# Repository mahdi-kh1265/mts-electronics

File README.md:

# mts-electronics

Analog RF, photodetector, and demodulation electronics for POSM's modulation-transfer spectroscopy (MTS) laser-locking system.

This repository contains two custom PCBs:

1. **`mts-clk`** — 10 MHz RF distribution and phase-control board for the EOM drive and MTS demodulation local oscillator.
2. **`mts-demod`** — photodiode front end, RF conditioning, analog mixer demodulation, and baseband error-signal generation.

The boards form the analog front end of POSM's rubidium MTS frequency lock.

---

## System Overview

# 1. `mts-clk` — 10 MHz Clock / Phase-Control Board

`mts-clk` takes a common 10 MHz RF source and generates the two coherent RF signals needed by the spectroscopy system:

* **EOM path** — drives the modulation chain associated with the electro-optic modulator.
* **DEMOD path** — provides the coherent local oscillator used by the analog MTS mixer.

Using a common source preserves coherence between modulation and demodulation.

# 2. `mts-demod` — Photodiode and Analog Demodulator

`mts-demod` converts the optical MTS signal into a low-frequency analog error signal suitable for digitization and feedback.

The board includes:

* FDS010 photodiode interface
* reverse-bias circuitry
* OPA858 transimpedance amplifier
* OPA695 second-stage RF amplifier
* 25 MHz RF cleanup filters
* RF splitting / diagnostic outputs
* conditioned 10 MHz LO path
* Mini-Circuits ADE-1+ mixer
* Mini-Circuits PLP-5+ post-mixer low-pass filter
* raw and demodulated monitor outputs

# 3. Repository Structure

```text
mts-electronics/
│
├── mts-clk/
│   ├── mts-clk.kicad_sch
│   ├── mts-clk.kicad_pcb
│   ├── mts-clk.kicad_pro
│   ├── libraries/
│   └── gerbers/
│
├── mts-demod/
│   ├── mts-demod.kicad_sch
│   ├── mts-demod.kicad_pcb
│   ├── mts-demod.kicad_pro
│   └── libraries/
│
├── LICENSE
└── README.md
```

The projects are currently stored in **KiCad 10** format.

---

# 4. Major Components

| Function                            | Part                      | Board       |
| ----------------------------------- | ------------------------- | ----------- |
| RF power splitter                   | Mini-Circuits TCP-2-10X   | `mts-clk`   |
| EOM-path RF amplifier               | ADI LTC6433-15            | `mts-clk`   |
| DEMOD-path RF amplifier             | ADI LTC6433-15            | `mts-clk`   |
| Voltage-controlled RF phase shifter | Mini-Circuits SCPHS-13.6+ | `mts-clk`   |
| Phase-control buffer                | TI OPA197                 | `mts-clk`   |
| Photodiode                          | Thorlabs FDS010           | `mts-demod` |
| First-stage TIA                     | TI OPA858                 | `mts-demod` |
| Second-stage amplifier              | TI OPA695                 | `mts-demod` |
| LO gain block                       | Mini-Circuits GVA-81      | `mts-demod` |
| Mixer                               | Mini-Circuits ADE-1+      | `mts-demod` |
| Post-mixer LPF                      | Mini-Circuits PLP-5+      | `mts-demod` |

Refer to the KiCad schematics for current component values and complete BOM information.

---

# 5. Bring-Up Sequence

These boards should be characterized independently before being connected to the complete laser lock.

## `mts-clk`

1. Verify resistance from each supply rail to ground before applying power.
2. Power the board with no external RF connections.
3. Verify all supply rails and amplifier bias conditions.
4. Apply a known 10 MHz RF input.
5. Measure the EOM output with an oscilloscope or spectrum analyzer.
6. Measure the DEMOD output.
7. Sweep the analog phase-control voltage.
8. Verify phase variation at 10 MHz relative to the EOM output.
9. Verify output amplitude remains within the intended range across the useful phase-control range.
10. Characterize phase versus control voltage and save the calibration curve.

## `mts-demod`

1. Verify all power rails before installing/connecting sensitive external hardware.
2. Verify photodiode reverse bias.
3. Illuminate the FDS010 with a controlled optical signal.
4. Measure the OPA858 TIA output.
5. Verify the OPA695 second-stage gain.
6. Verify the 25 MHz cleanup-filter response.
7. Apply a known 10 MHz DEMOD/LO signal.
8. Verify the GVA-81 LO chain.
9. Verify adequate LO drive at the ADE-1+.
10. Observe the raw mixer IF.
11. Verify the PLP-5+ output.
12. Sweep relative RF/LO phase and confirm the expected quadrature dependence.
13. Only after analog characterization, connect the ADC / FPGA system.

---

# 10. Characterization Data to Add

The schematic captures the intended design. Measured hardware performance should be added separately once boards are assembled.

Useful measurements include:

### CLK board

* EOM output power at 10 MHz
* DEMOD output power at 10 MHz
* EOM-to-DEMOD relative phase range
* phase versus control voltage
* amplitude versus phase-control voltage
* harmonic distortion
* broadband noise
* output return loss / matching

### DEMOD board

* TIA transimpedance
* TIA noise spectral density
* complete photodiode-path gain
* 25 MHz filter response
* mixer conversion gain/loss
* LO level at ADE-1+
* baseband transfer function
* analog error-signal noise
* output offset
* usable MTS discriminator slope
* channel saturation limits

Measured data should eventually be stored under a dedicated directory such as:

```text
measurements/
├── mts-clk/
│   ├── phase_vs_control_voltage.csv
│   ├── output_spectrum/
│   └── network_analyzer/
│
└── mts-demod/
    ├── tia_noise/
    ├── rf_transfer_function/
    ├── mixer_characterization/
    └── mts_error_signal/
```
# License

Released under the license included in [`LICENSE`](LICENSE).

---

## POSM

**Photonics and Optical Sciences Club at Minnesota**
University of Minnesota

[POSM website](https://posmphotonics.org/)

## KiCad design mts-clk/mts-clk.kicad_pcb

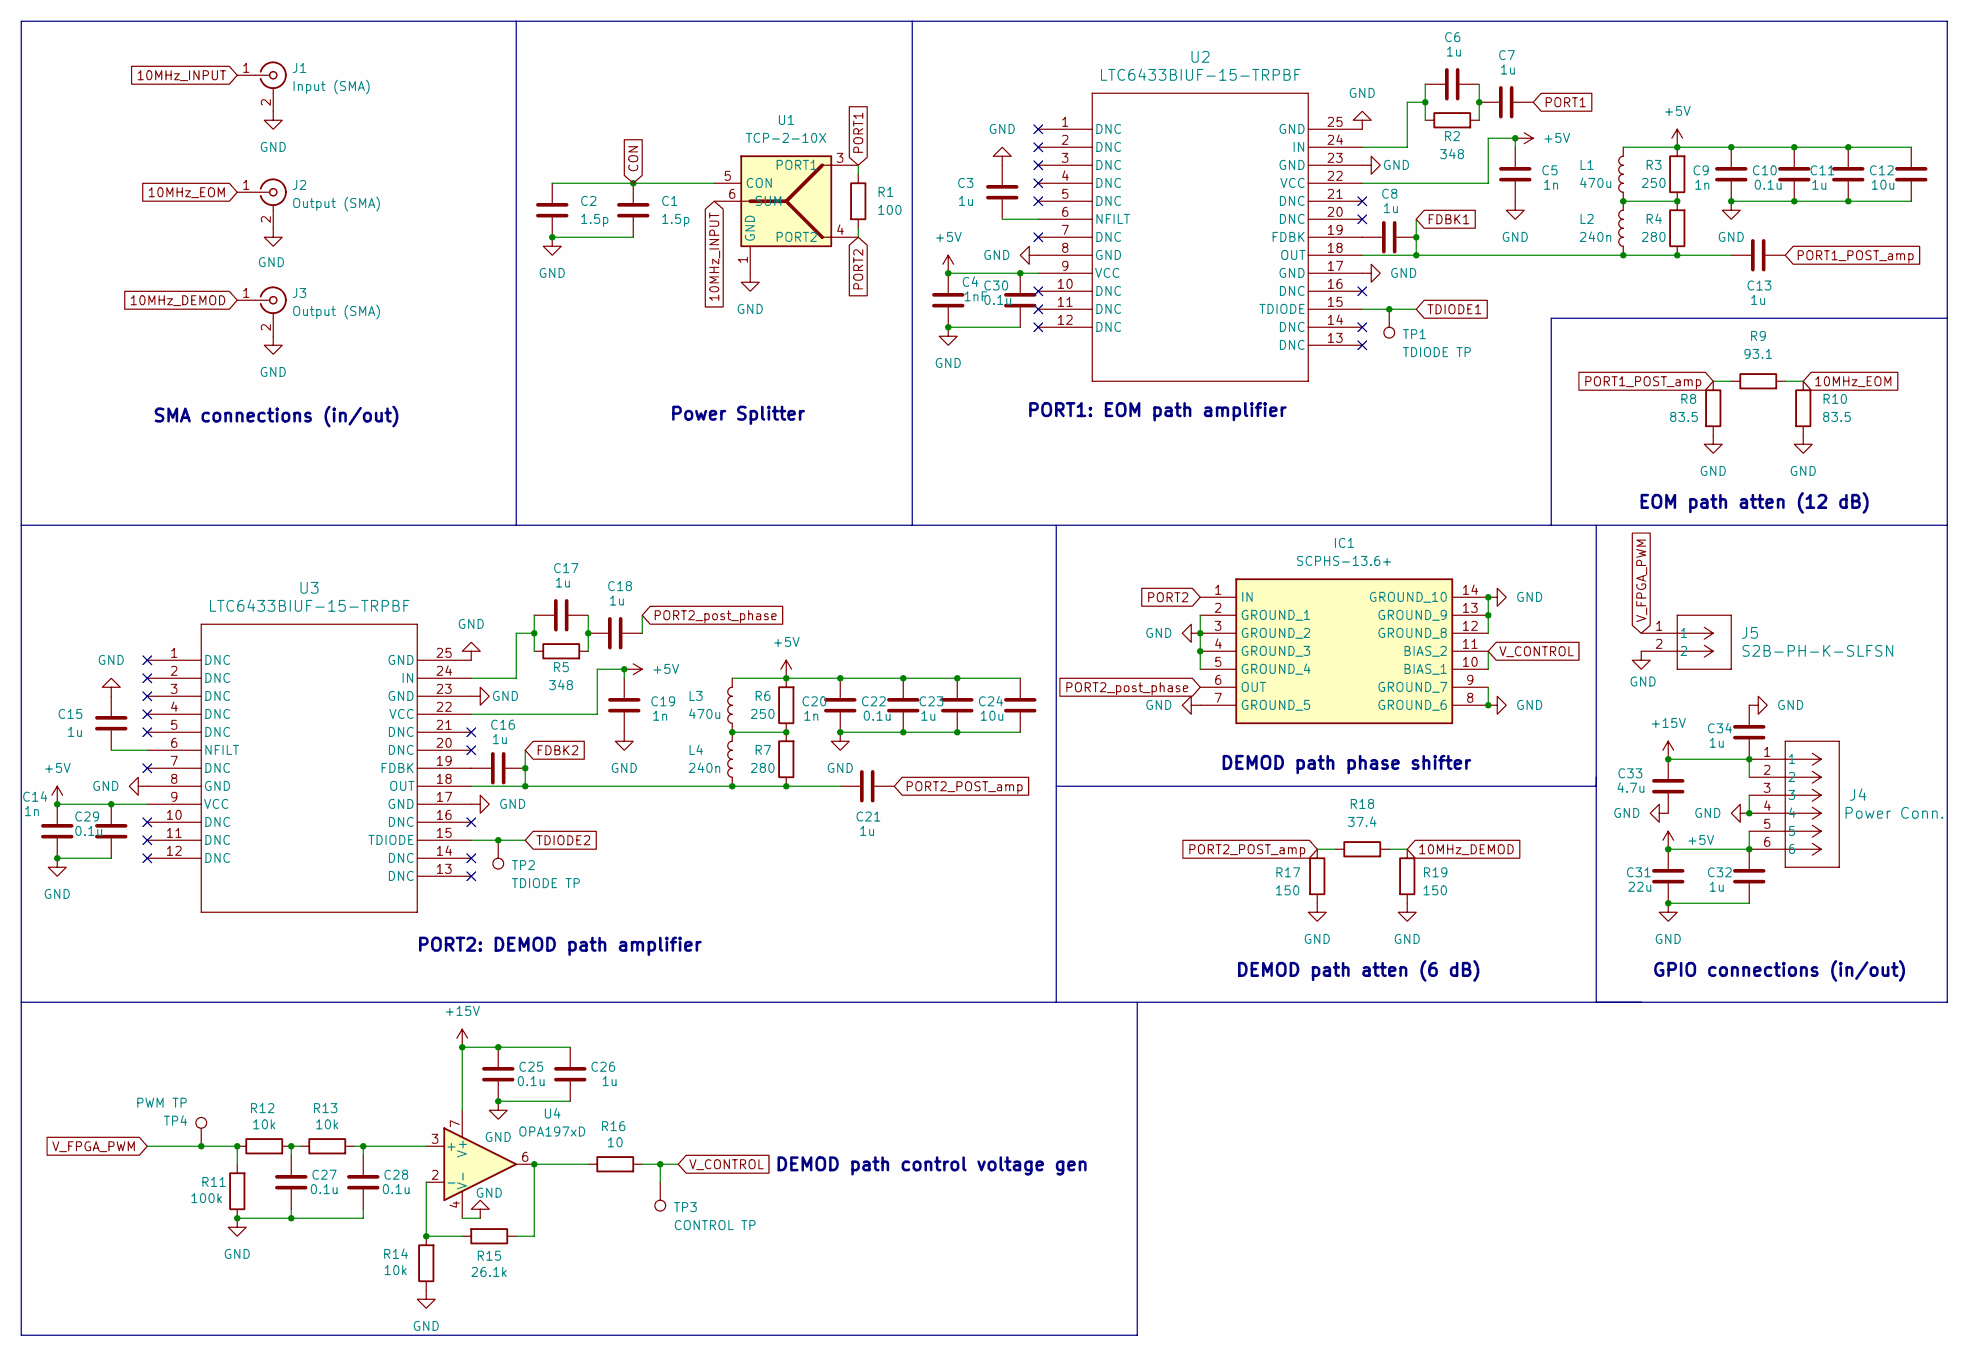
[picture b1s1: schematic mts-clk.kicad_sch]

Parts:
C1, C2: 1.5p; C_0402_1005Metric
C3, C6, C7, C8, C11, C13, C15, C16, C17, C18, C21, C23, C26: 1u; C_0805_2012Metric
C4: 1nF; C_0402_1005Metric
C5, C9, C14, C19, C20: 1n; C_0402_1005Metric
C10, C22, C29, C30: 0.1u; C_0603_1608Metric
C12, C24: 10u; C_0805_2012Metric
C25, C27, C28: 0.1u; C_0805_2012Metric
C31: 22u; C_1206_3216Metric
C32, C34: 1u; C_0603_1608Metric
C33: 4.7u; C_1206_3216Metric
IC1: SCPHS-13.6+; SCPHS136; Manufacturer_Part_Number SCPHS-13.6+
J1: Input (SMA); CONN_SMA-J-P-H-ST-TH1_SAI
J2, J3: Output (SMA); CONN_SMA-J-P-H-ST-TH1_SAI
J4: Power Conn.; CONN_SD-43045-005_06_MOL
J5: S2B-PH-K-SLFSN; CONN_S2B-PH-K-S_JST
L1, L3: 470u; L_Coilcraft_LPS5030
L2, L4: 240n; L_0603_1608Metric
R1: 100; R_0603_1608Metric
R2, R5: 348; R_0805_2012Metric
R3, R6: 250; R_0603_1608Metric
R4, R7: 280; R_0603_1608Metric
R8, R10: 83.5; R_0603_1608Metric
R9: 93.1; R_0603_1608Metric
R11: 100k; R_0603_1608Metric
R12, R13, R14: 10k; R_0603_1608Metric
R15: 26.1k; R_0603_1608Metric
R16: 10; R_0603_1608Metric
R17, R19: 150; R_0603_1608Metric
R18: 37.4; R_0603_1608Metric
TP1, TP2: TDIODE TP; TestPoint_Keystone_5015_Micro_Mini
TP3: CONTROL TP; TestPoint_Keystone_5015_Micro_Mini
TP4: PWM TP; TestPoint_Keystone_5015_Micro_Mini
U1: TCP-2-10X; Mini-Circuits_DB1627
U2, U3: LTC6433BIUF-15-TRPBF; UF_24_ADI
U4: OPA197xD; SOIC-8_3.9x4.9mm_P1.27mm

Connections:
10MHz_DEMOD: J3.1 (In), R18.2, R19.1
10MHz_EOM: J2.1 (In), R9.2, R10.1
10MHz_INPUT: J1.1 (In), U1.6 (SUM)
+5V: C4.2, C5.2, C9.2, C10.2, C11.2, C12.2, C14.2, C19.2, C20.2, C22.2, C23.2, C24.2, C29.2, C30.2, C31.2, C32.2, J4.5, J4.6, L1.2, L3.2, R3.2, R6.2, U2.9 (VCC), U2.22 (VCC), U3.9 (VCC), U3.22 (VCC)
+15V: C25.1, C26.1, C33.1, C34.1, J4.1, J4.2, U4.7 (V+)
FDBK1: C8.1, C13.2, L2.1, R4.1, U2.18 (OUT)
FDBK2: C16.1, C21.2, L4.1, R7.1, U3.18 (OUT)
GND: C1.2, C2.1, C3.1, C4.1, C5.1, C9.1, C10.1, C11.1, C12.1, C14.1, C15.1, C19.1, C20.1, C22.1, C23.1, C24.1, C25.2, C26.2, C27.2, C28.2, C29.1, C30.1, C31.1, C32.1, C33.2, C34.2, IC1.2 (GROUND_1), IC1.3 (GROUND_2), IC1.4 (GROUND_3), IC1.5 (GROUND_4), IC1.7 (GROUND_5), IC1.8 (GROUND_6), IC1.9 (GROUND_7), IC1.12 (GROUND_8), IC1.13 (GROUND_9), IC1.14 (GROUND_10), J1.2 (Ext), J1.3, J1.4, J1.5, J2.2 (Ext), J2.3, J2.4, J2.5, J3.2 (Ext), J3.3, J3.4, J3.5, J4.3, J4.4, J5.2, R8.2, R10.2, R11.1, R14.1, R17.2, R19.2, U1.1 (GND), U2.8 (GND), U2.17 (GND), U2.23 (GND), U2.25 (GND), U3.8 (GND), U3.17 (GND), U3.23 (GND), U3.25 (GND), U4.4 (V-)
unnamed: C6.1, C7.2, R2.2
unnamed: C17.1, C18.2, R5.2
unnamed: C27.1, R12.2, R13.1
unnamed: L1.1, L2.2, R3.1, R4.2
unnamed: L3.1, L4.2, R6.1, R7.2
unnamed: R15.1, R16.1, U4.6
unnamed: C8.2, U2.19 (FDBK)
unnamed: C6.2, R2.1, U2.24 (IN)
unnamed: C3.2, U2.6 (NFILT)
unnamed: C16.2, U3.19 (FDBK)
unnamed: C17.2, R5.1, U3.24 (IN)
unnamed: C15.2, U3.6 (NFILT)
unnamed: C28.1, R13.2, U4.3 (+)
unnamed: R14.2, R15.2, U4.2 (-)
PORT1: C7.1, R1.1, U1.3 (PORT1)
PORT1_POST_amp: C13.1, R8.1, R9.1
PORT2: IC1.1 (IN), R1.2, U1.4 (PORT2)
PORT2_POST_amp: C21.1, R17.1, R18.1
PORT2_post_phase: C18.1, IC1.6 (OUT)
TDIODE1: TP1.1 (1_1), U2.15 (TDIODE)
TDIODE2: TP2.1 (1_1), U3.15 (TDIODE)
V_CONTROL: IC1.10 (BIAS_1), IC1.11 (BIAS_2), R16.2, TP3.1 (1_1)
V_FPGA_PWM: J5.1, R11.2, R12.1, TP4.1 (1_1)

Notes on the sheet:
PORT1: EOM path amplifier
SMA connections (in/out)
DEMOD path phase shifter
DEMOD path control voltage gen
DEMOD path atten (6 dB)
GPIO connections (in/out)
Power Splitter
EOM path atten (12 dB)
PORT2: DEMOD path amplifier

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
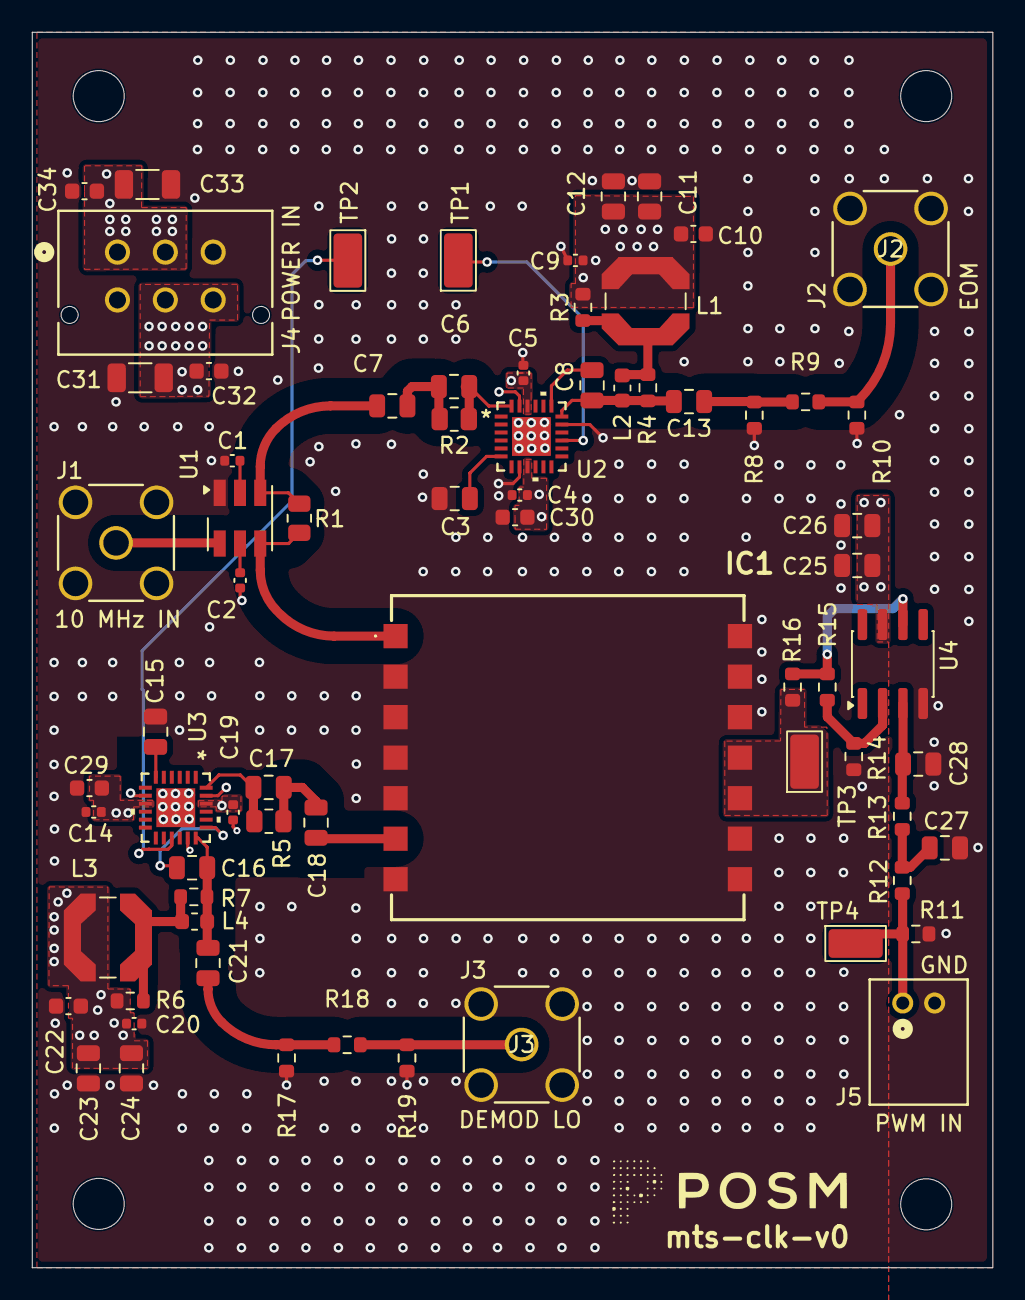
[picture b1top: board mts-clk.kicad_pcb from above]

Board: 4 copper layers, 60.2 x 77.5 mm, 71 parts (0 on the bottom side), 33 nets.

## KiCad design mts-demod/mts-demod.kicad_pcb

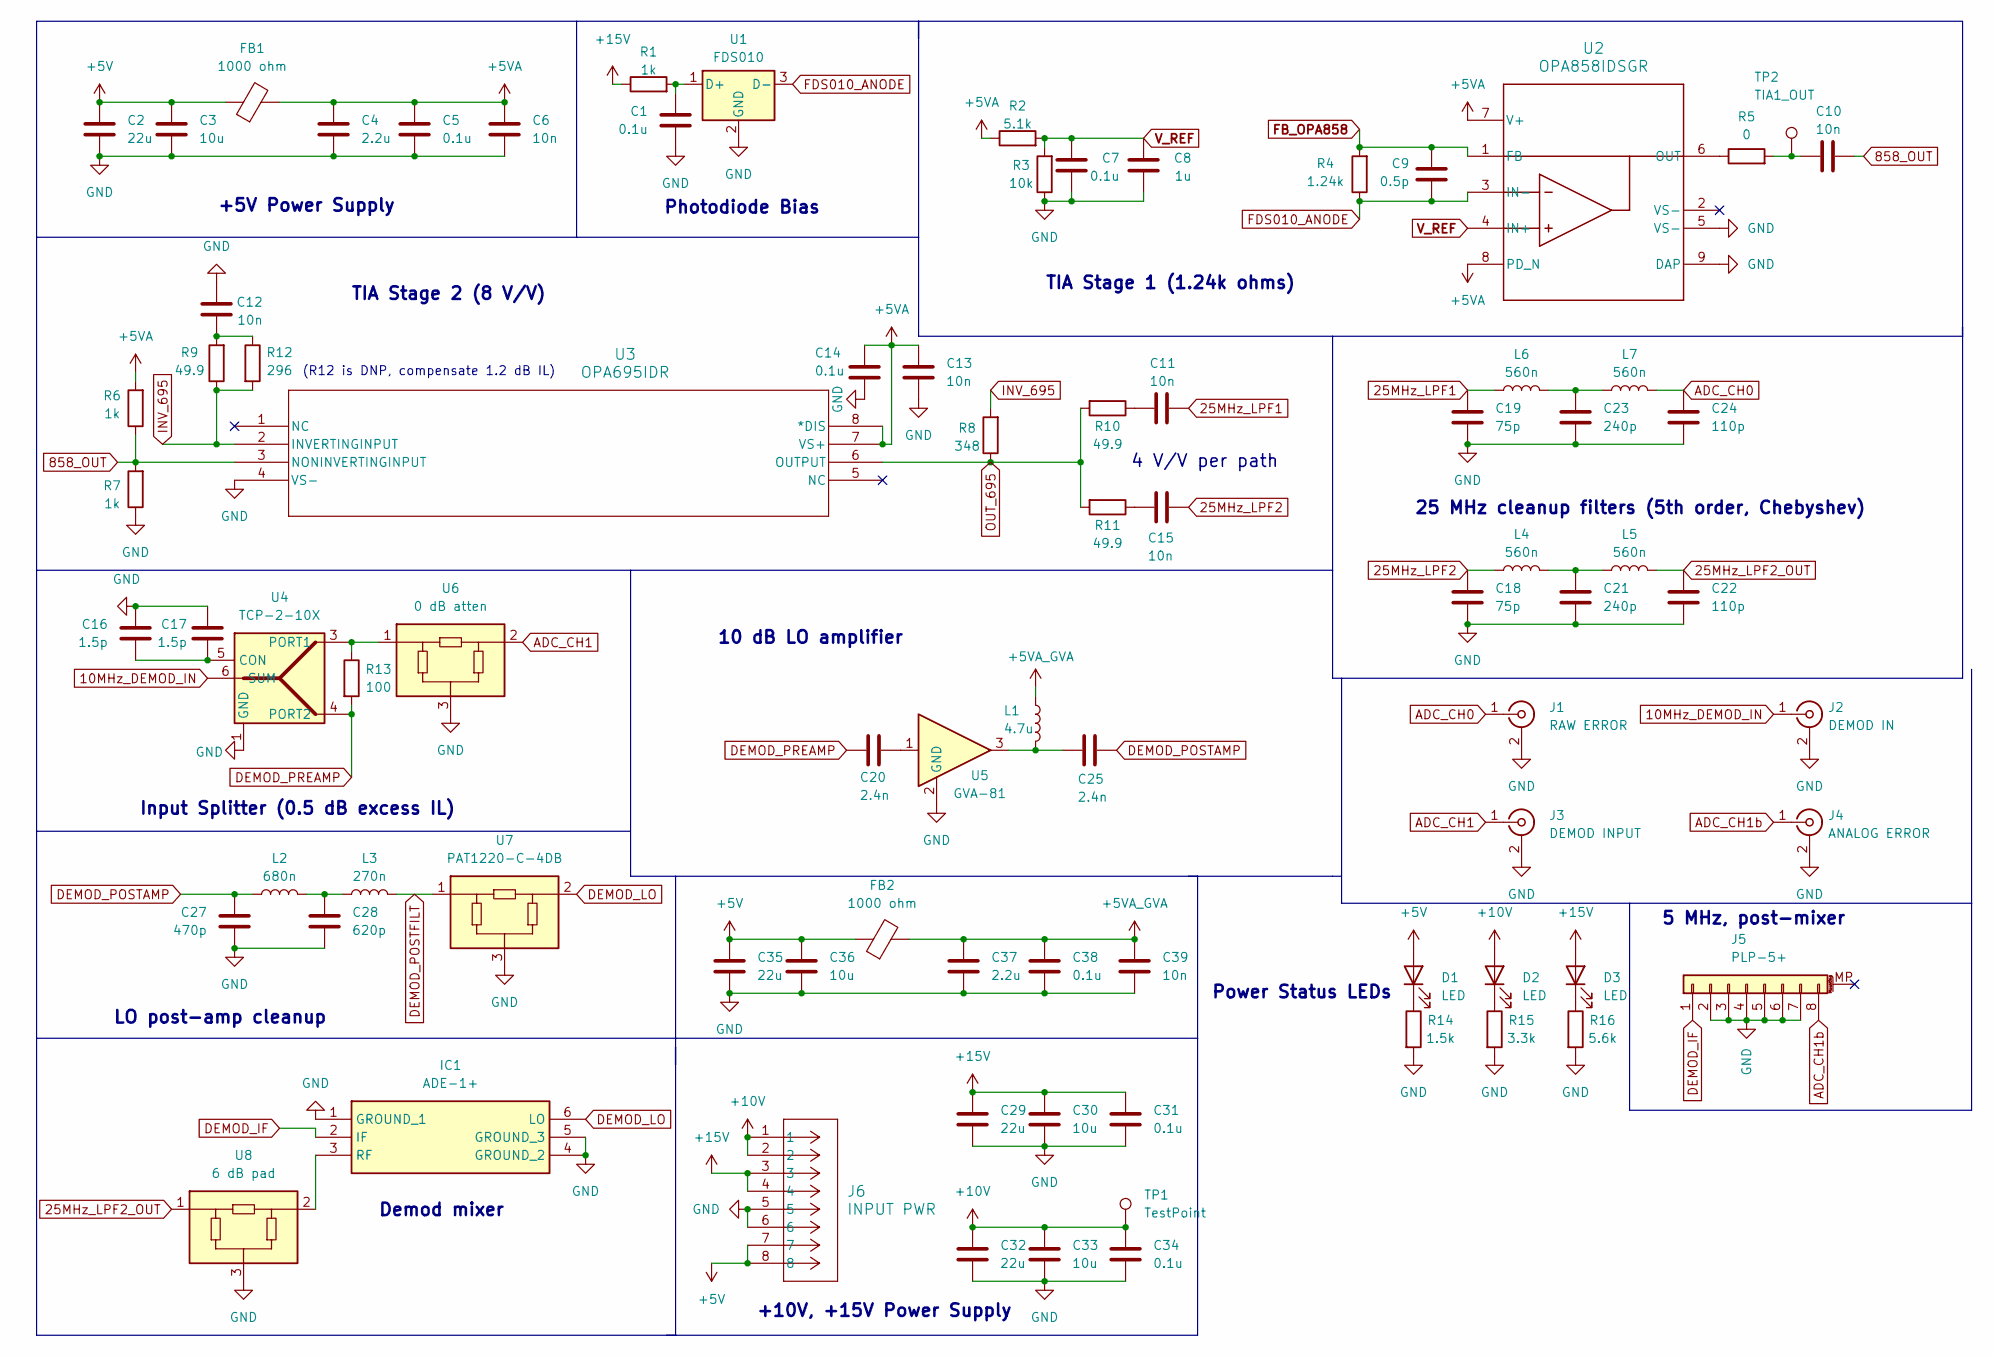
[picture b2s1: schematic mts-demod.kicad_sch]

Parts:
C1, C5, C7, C14, C31, C34, C38: 0.1u; C_0603_1608Metric
C2, C29, C32, C35: 22u; C_0805_2012Metric
C3, C30, C33, C36: 10u; C_0805_2012Metric
C4, C37: 2.2u; C_0603_1608Metric
C6, C10, C11, C12, C13, C15, C39: 10n; C_0402_1005Metric
C8: 1u; C_0603_1608Metric
C9: 0.5p; C_0402_1005Metric
C16, C17: 1.5p; C_0402_1005Metric
C18, C19: 75p; C_0805_2012Metric
C20, C25: 2.4n; C_0402_1005Metric
C21, C23: 240p; C_0805_2012Metric
C22, C24: 110p; C_0805_2012Metric
C27: 470p; C_0805_2012Metric
C28: 620p; C_0805_2012Metric
D1, D2, D3: LED; LED_0603_1608Metric
FB1, FB2: 1000 ohm; L_0805_2012Metric
IC1: ADE-1+; ADE1; Mouser Part Number 139-ADE-1
J1: RAW ERROR; CONN_SMA-J-P-H-ST-TH1_SAI
J2: DEMOD IN; CONN_SMA-J-P-H-ST-TH1_SAI
J3: DEMOD INPUT; CONN_SMA-J-P-H-ST-TH1_SAI
J4: ANALOG ERROR; CONN_SMA-J-P-H-ST-TH1_SAI
J5: PLP-5+; MINI-CIRCUITS_A01_CERN
J6: INPUT PWR; CONN_SD-43045-005_08_MOL
L1: 4.7u; L_0603_1608Metric
L2: 680n; L_0805_2012Metric
L3: 270n; L_0805_2012Metric
L4, L5, L6, L7: 560n; L_0805_2012Metric
R1, R6, R7: 1k; C_0603_1608Metric
R2: 5.1k; R_0603_1608Metric
R3: 10k; R_0603_1608Metric
R4: 1.24k; R_0603_1608Metric
R5: 0; R_0402_1005Metric
R8: 348; R_0402_1005Metric
R9: 49.9; C_0603_1608Metric
R10, R11: 49.9; R_0402_1005Metric
R12: 296; C_0603_1608Metric
R13: 100; C_0603_1608Metric
R14: 1.5k; C_0603_1608Metric
R15: 3.3k; C_0603_1608Metric
R16: 5.6k; C_0603_1608Metric
TP1: TestPoint; TestPoint_Keystone_5015_Micro_Mini
TP2: TIA1_OUT; TestPoint_Keystone_5015_Micro_Mini
U1: FDS010; TO-39-3
U2: OPA858IDSGR; DSG0008A
U3: OPA695IDR; D8
U4: TCP-2-10X; Mini-Circuits_DB1627
U5: GVA-81; SOT-89-3
U6: 0 dB atten; RF_Attenuator_Susumu_PAT1220
U7: PAT1220-C-4DB; RF_Attenuator_Susumu_PAT1220
U8: 6 dB pad; RF_Attenuator_Susumu_PAT1220

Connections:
10MHz_DEMOD_IN: J2.1 (In), U4.6 (SUM)
25MHz_LPF1: C11.2, C19.1, L6.1
25MHz_LPF2: C15.2, C18.1, L4.1
25MHz_LPF2_OUT: C22.1, L5.2, U8.1
858_OUT: C10.2, R6.1, R7.2, U3.3 (NONINVERTINGINPUT)
+5V: C2.1, C3.1, C35.1, C36.1, D1.2 (A), FB1.1, FB2.1, J6.7, J6.8; also elsewhere on the board
+5VA: C4.1, C5.1, C6.1, C13.1, C14.2, FB1.2, R2.1, R6.2, U2.7 (V+), U2.8 (PD_N), U3.7 (VS+), U3.8 (*DIS)
+5VA_GVA: C37.1, C38.1, C39.1, FB2.2, L1.1; also elsewhere on the board
+10V: C32.1, C33.1, C34.1, D2.2 (A), J6.1, J6.2, TP1.1; also elsewhere on the board
+15V: C29.1, C30.1, C31.1, D3.2 (A), J6.3, J6.4, R1.1; also elsewhere on the board
ADC_CH0: C24.1, J1.1 (In), L7.2
ADC_CH1: J3.1 (In), U6.2
ADC_CH1b: J4.1 (In), J5.8
DEMOD_IF: IC1.2 (IF), J5.1
DEMOD_LO: IC1.6 (LO), U7.2
DEMOD_POSTAMP: C25.1, C27.2, L2.1
DEMOD_POSTFILT: L3.2, U7.1
DEMOD_PREAMP: C20.2, R13.2, U4.4 (PORT2)
FB_OPA858: C9.2, R4.2, U2.1 (FB)
FDS010_ANODE: C9.1, R4.1, U1.3 (D-), U2.3 (IN-)
GND: C1.2, C2.2, C3.2, C4.2, C5.2, C6.2, C7.2, C8.2, C12.1, C13.2, C14.1, C16.2, C17.2, C18.2, C19.2, C21.2, C22.2, C23.2, C24.2, C27.1, C28.1, C29.2, C30.2, C31.2, C32.2, C33.2, C34.2, C35.2, C36.2, C37.2, C38.2, C39.2, IC1.1 (GROUND_1), IC1.4 (GROUND_2), IC1.5 (GROUND_3), J1.2 (Ext), J1.3, J1.4, J1.5, J2.2 (Ext), J2.3, J2.4, J2.5, J3.2 (Ext), J3.3, J3.4, J3.5, J4.2 (Ext), J4.3, J4.4, J4.5, J5.2, J5.3, J5.4, J5.5, J5.6, J5.7, J6.5, J6.6, R3.1, R7.1, R14.2, R15.2, R16.2, U1.2 (GND), U2.5 (VS-), U2.9 (DAP), U3.4 (VS-), U4.1 (GND), U5.2 (GND_2), U6.3, U7.3, U8.3; also elsewhere on the board
INV_695: R8.2, R9.1, R12.2, U3.2 (INVERTINGINPUT)
unnamed 22: C10.1, R5.2, TP2.1; also elsewhere on the board
unnamed: C11.1, R10.1
unnamed: C12.2, R9.2, R12.1
unnamed: C15.1, R11.1
unnamed: C20.1, U5.1
unnamed: C21.1, L4.2, L5.1
unnamed: C23.1, L6.2, L7.1
unnamed: C25.2, L1.2, U5.3
unnamed: C28.2, L2.2, L3.1
unnamed 31: D1.1 (K), R14.1; also elsewhere on the board
unnamed 32: D2.1 (K), R15.1; also elsewhere on the board
unnamed 33: D3.1 (K), R16.1; also elsewhere on the board
unnamed: IC1.3 (RF), U8.2
unnamed: C1.1, R1.2, U1.1 (D+)
unnamed: R5.1, U2.6 (OUT)
unnamed: R13.1, U4.3 (PORT1), U6.1
OUT_695: R8.1, R10.2, R11.2, U3.6 (OUTPUT)
V_REF: C7.1, C8.1, R2.2, R3.2, U2.4 (IN+)

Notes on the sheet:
(R12 is DNP, compensate 1.2 dB IL)
+10V, +15V Power Supply
+5V Power Supply
Photodiode Bias
Power Status LEDs
25 MHz cleanup filters (5th order, Chebyshev)
10 dB LO amplifier
4 V/V per path
LO post-amp cleanup
TIA Stage 2 (8 V/V)
TIA Stage 1 (1.24k ohms)
5 MHz, post-mixer
Input Splitter (0.5 dB excess IL)
Demod mixer

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
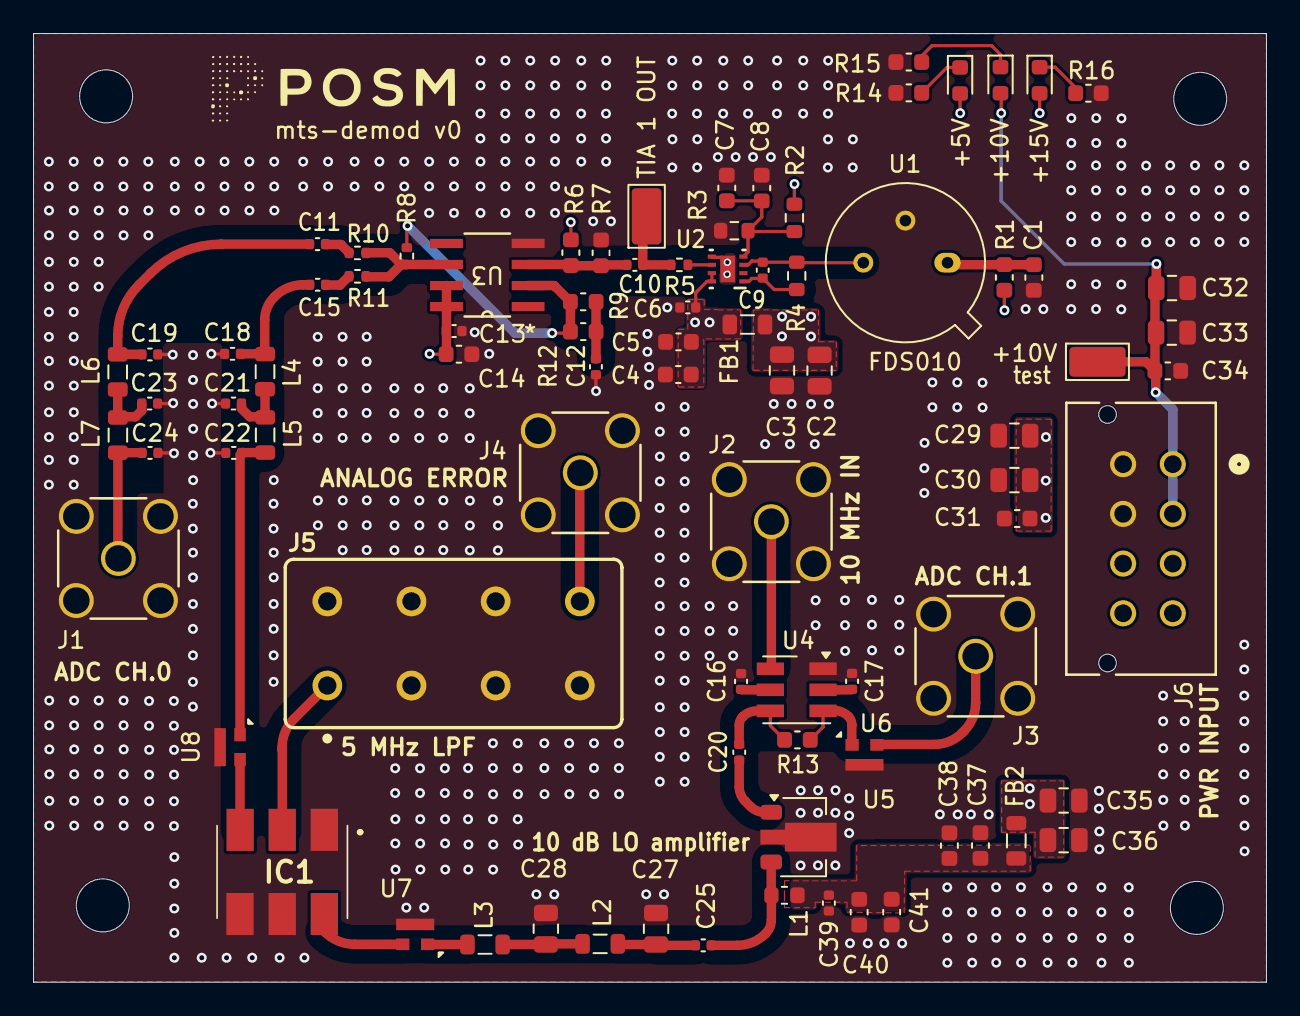
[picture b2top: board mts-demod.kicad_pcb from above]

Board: 4 copper layers, 74.4 x 57.3 mm, 85 parts (0 on the bottom side), 42 nets.

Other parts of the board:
+5V, +10V#2, +15V: LED; LED_0603_1608Metric
+10V: TestPoint; TestPoint_Keystone_5015_Micro_Mini
C40, C41: 0.1u; C_0603_1608Metric
TIA 1 OUT: TIA1_OUT; TestPoint_Keystone_5015_Micro_Mini

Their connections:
+5V: +5V.2 (A); also elsewhere on the board
+5VA_GVA: C40.1, C41.1; also elsewhere on the board
+10V: +10V.1 (1_1), +10V#2.2 (A); also elsewhere on the board
+15V: +15V.2 (A); also elsewhere on the board
GND: C40.2, C41.2; also elsewhere on the board
unnamed 22: TIA 1 OUT.1 (1_1); also elsewhere on the board
unnamed 31: +5V.1 (K); also elsewhere on the board
unnamed 32: +10V#2.1 (K); also elsewhere on the board
unnamed 33: +15V.1 (K); also elsewhere on the board
